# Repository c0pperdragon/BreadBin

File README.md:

# BreadBin computer
A CPU made of 7400 logic on breadboards - inside a bread bin ;-) 

## Current design 

After various experiments and failed attempts to design a 7400-based computer, I came to a quite minimalistic
8-bit approach which is nevertheless pretty versatile and can utilize a surprisingly large amount of memory
resources. The CPU core itself executes its program from a static 64K flash memory and can access 32 bytes of
internal RAM (which can be considered registers for all practical purposes). Access to the external memory 
area (up to 16MB of address space) allows addition of RAM, ROM and memory mapped IO. In the current setup this
directly mirrors the capabilities of my [OS816 reference design](https://github.com/c0pperdragon/OS816).

## Computer case

With the CPU already built so nicely on an actual wooden board, I had the idea to put it together with
the rest of the computer into a matching bread bin. Because the machine will not require any ventilation this
will keep the dust out quite reliably.

## On bread boards

Since a very long time I wanted to design my own CPU and build it from smaller parts, preferable 
on bread boards. My main problem with the approach were my bad experiences with bread boards as a whole,
as they seemed to be too unreliable for anything more serious than arduino tinkering.
As it turns out it is only a matter of using high-quality boards and cabling to get a reliably working
build. The boards I now use (BB830 from BusBoard) are quite expensive, but worth every penny 
and give me very little trouble.

In previous attempts I had much trouble to get a stable ground reference accross all the individual boards.
So this time I directly soldered together ground rails of parallel boards with silver wire on the bottom
and then placed the boards on top of a large plane of aluminium foil. This foil should make good contact to all
the silver ground wires to connect them together and additionally work as shielding. 
So far this works pretty good.

When using this kind of setup it is important to also use a matching logic family of chips. 74AC, 74ACT, 74LVC or 
others have a very fast switching characteristics. This is great for many applications but in a large build with
long and unshielded cables, their brutally steep signal edges wreck havoc with signal integritiy.
So I settled for the moderately fast and well-behaved 74HC logic ICs with only a few 74AC parts to speed up the ALU.

## Software

One of the hardest parts of home-made computers is to actually build all the software to make the machine useful.
To get the benefit of existing software, the breadboard computer core is designed to emulate the existing CPU
65C816. Together with 512K RAM and 512K Flash and identical IO capabilities, this now is a completely software 
compatible replica of the OS816 system - running at a lower overall speed, of course.

To properly stay in the "bread" theme, the emulator is called [Bernd](bernd) or BER/ND (if you like a 
more technical appearance). People familiar with the german TV station "Kinderkanal" will recognize the reference.

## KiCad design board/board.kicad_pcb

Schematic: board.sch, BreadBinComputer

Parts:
C1, C2: 33pF; C_Disc_D4.7mm_W2.5mm_P5.00mm
C3: 10uF; C_Disc_D4.7mm_W2.5mm_P5.00mm
C4: 100uF; CP_Radial_D10.0mm_P5.00mm
IN1: 74HC245; DIP-20_W7.62mm
INV1: 74HC04; DIP-14_W7.62mm
JIN1: Conn_01x08; PinHeader_1x08_P2.54mm_Vertical
JOUT1: Conn_01x08; PinHeader_1x08_P2.54mm_Vertical
JPOWER1: Conn_01x02; PinHeader_1x02_P2.54mm_Vertical
OR2: 74HC32; DIP-14_W7.62mm
OUT1: 74HC574; DIP-20_W7.62mm
R1: 1k; R_Axial_DIN0204_L3.6mm_D1.6mm_P7.62mm_Horizontal
R2: 1M; R_Axial_DIN0204_L3.6mm_D1.6mm_P7.62mm_Horizontal
R3: 33k; R_Axial_DIN0204_L3.6mm_D1.6mm_P7.62mm_Horizontal
RAM1: AS6C4008; DIP-32_W15.24mm
RES1: 74HC164; DIP-14_W7.62mm
RN1: 10k; R_Array_SIP9
ROM1: SST39SF040; DIP-32_W15.24mm
TIM1: NE555; DIP-8_W7.62mm
Y1: Crystal; Crystal_HC18-U_Vertical

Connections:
/AD0: RAM1.1, ROM1.12; also elsewhere on the board
/AD1: RAM1.2, ROM1.11; also elsewhere on the board
/AD2: RAM1.3, ROM1.10; also elsewhere on the board
/AD3: RAM1.4, ROM1.9; also elsewhere on the board
/AD4: RAM1.5, ROM1.8; also elsewhere on the board
/AD5: RAM1.6, ROM1.7; also elsewhere on the board
/AD6: RAM1.7, ROM1.6; also elsewhere on the board
/AD7: RAM1.8, ROM1.5; also elsewhere on the board
/AD8: RAM1.27, ROM1.27; also elsewhere on the board
/AD9: RAM1.28, ROM1.26; also elsewhere on the board
/AD10: RAM1.31, ROM1.23; also elsewhere on the board
/AD11: RAM1.30, ROM1.25; also elsewhere on the board
/AD12: RAM1.9, ROM1.4; also elsewhere on the board
/AD13: RAM1.26, ROM1.28; also elsewhere on the board
/AD14: RAM1.25, ROM1.29; also elsewhere on the board
/AD15: RAM1.10, ROM1.3; also elsewhere on the board
/AD16: RAM1.11, ROM1.2; also elsewhere on the board
/AD17: RAM1.23, ROM1.30; also elsewhere on the board
/AD18: RAM1.12, ROM1.1; also elsewhere on the board
/AD22: INV1.13, OR2.1; also elsewhere on the board
/AD23: INV1.11, OR2.2, OR2.4; also elsewhere on the board
/BreadBinCPU/CLK: INV1.6, RES1.8; also elsewhere on the board
/BreadBinCPU/RES#: RES1.13; also elsewhere on the board
/D0: IN1.9 (A7), OUT1.9, RAM1.13, ROM1.13; also elsewhere on the board
/D1: IN1.8 (A6), OUT1.8, RAM1.14, ROM1.14; also elsewhere on the board
/D2: IN1.7 (A5), OUT1.7, RAM1.15, ROM1.15; also elsewhere on the board
/D3: IN1.6 (A4), OUT1.6, RAM1.17, ROM1.17; also elsewhere on the board
/D4: IN1.5 (A3), OUT1.5, RAM1.18, ROM1.18; also elsewhere on the board
/D5: IN1.4 (A2), OUT1.4, RAM1.19, ROM1.19; also elsewhere on the board
/D6: IN1.3 (A1), OUT1.3, RAM1.20, ROM1.20; also elsewhere on the board
/D7: IN1.2 (A0), OUT1.2, RAM1.21, ROM1.21; also elsewhere on the board
/IOSEL#: OR2.6, OR2.9, OR2.12
/RAMSEL#: OR2.3, RAM1.22
/RD#: OR2.13, RAM1.24, ROM1.24; also elsewhere on the board
/ROMSEL#: INV1.10, ROM1.22
/WR#: OR2.10, RAM1.29, ROM1.31; also elsewhere on the board
unnamed: C1.1, R1.2, Y1.2
unnamed: C2.1, INV1.1, R2.2, Y1.1
unnamed: C3.1, R3.1, TIM1.2 (TR), TIM1.6 (THR)
unnamed: IN1.11 (B7), JIN1.1, RN1.9
unnamed: IN1.12 (B6), JIN1.2, RN1.8
unnamed: IN1.13 (B5), JIN1.3, RN1.7
unnamed: IN1.14 (B4), JIN1.4, RN1.6
unnamed: IN1.15 (B3), JIN1.5, RN1.5
unnamed: IN1.16 (B2), JIN1.6, RN1.4
unnamed: IN1.17 (B1), JIN1.7, RN1.3
unnamed: IN1.18 (B0), JIN1.8, RN1.2
unnamed: IN1.19 (CE), OR2.11
unnamed: INV1.2, INV1.3, R1.1, R2.1
unnamed: INV1.4, INV1.5, INV1.9
unnamed: INV1.12, OR2.5
unnamed: JOUT1.1, OUT1.12
unnamed: JOUT1.2, OUT1.13
unnamed: JOUT1.3, OUT1.14
unnamed: JOUT1.4, OUT1.15
unnamed: JOUT1.5, OUT1.16
unnamed: JOUT1.6, OUT1.17
unnamed: JOUT1.7, OUT1.18
unnamed: JOUT1.8, OUT1.19
unnamed: OR2.8, OUT1.11
unnamed: RES1.9, TIM1.3 (Q)

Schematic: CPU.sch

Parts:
DEC1: 74HC138; DIP-16_W7.62mm
GATE1: 74HC541; DIP-20_W7.62mm
IR1: 74HC574; DIP-20_W7.62mm
MCODE1: SST39SF040; DIP-32_W15.24mm
OP1: 74HC377; DIP-20_W7.62mm
OR1: 74HC32; DIP-14_W7.62mm
PC1, PC2: 74HC163; DIP-16_W7.62mm
PC3: 74HC377; DIP-20_W7.62mm
REG1: IDT71256; DIP-28_W7.62mm
UA1: 74HC377; DIP-20_W7.62mm
UB1: 74HC377; DIP-20_W7.62mm
UC1: 74HC377; DIP-20_W7.62mm

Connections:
/AD0: OR1.10, UA1.2, UB1.3; also elsewhere on the board
/AD1: UA1.5, UB1.4; also elsewhere on the board
/AD2: UA1.6, UB1.7; also elsewhere on the board
/AD3: UA1.9, UB1.8; also elsewhere on the board
/AD4: UA1.12, UB1.13; also elsewhere on the board
/AD5: UA1.15, UB1.14; also elsewhere on the board
/AD6: UA1.16, UB1.17; also elsewhere on the board
/AD7: UA1.19, UB1.18; also elsewhere on the board
/AD8: UB1.2, UC1.3; also elsewhere on the board
/AD9: UB1.5, UC1.4; also elsewhere on the board
/AD10: UB1.6, UC1.7; also elsewhere on the board
/AD11: UB1.9, UC1.8; also elsewhere on the board
/AD12: UB1.12, UC1.13; also elsewhere on the board
/AD13: UB1.15, UC1.14; also elsewhere on the board
/AD14: UB1.16, UC1.17; also elsewhere on the board
/AD15: UB1.19, UC1.18; also elsewhere on the board
/AD16: UC1.2; also elsewhere on the board
/AD17: UC1.5; also elsewhere on the board
/AD18: UC1.6; also elsewhere on the board
/AD22: UC1.16; also elsewhere on the board
/AD23: UC1.19; also elsewhere on the board
/BreadBinCPU/ALU/OP0: OP1.9; also elsewhere on the board
/BreadBinCPU/ALU/OP1: OP1.6; also elsewhere on the board
/BreadBinCPU/ALU/OP2: OP1.5; also elsewhere on the board
/BreadBinCPU/ALU/OP3: OP1.2; also elsewhere on the board
/BreadBinCPU/ALU/Q0: GATE1.2 (A0); also elsewhere on the board
/BreadBinCPU/ALU/Q1: GATE1.3 (A1); also elsewhere on the board
/BreadBinCPU/ALU/Q2: GATE1.4 (A2); also elsewhere on the board
/BreadBinCPU/ALU/Q3: GATE1.5 (A3); also elsewhere on the board
/BreadBinCPU/ALU/Q4: GATE1.6 (A4); also elsewhere on the board
/BreadBinCPU/ALU/Q5: GATE1.7 (A5); also elsewhere on the board
/BreadBinCPU/ALU/Q6: GATE1.8 (A6); also elsewhere on the board
/BreadBinCPU/ALU/Q7: GATE1.9 (A7); also elsewhere on the board
/BreadBinCPU/BRA#: OR1.8, PC1.9 (~PE), PC2.9 (~PE)
/BreadBinCPU/C3: UC1.9
/BreadBinCPU/C4: UC1.12
/BreadBinCPU/C5: UC1.15
/BreadBinCPU/CLK: GATE1.1 (G1), IR1.11, OP1.11, OR1.1, OR1.12, PC1.2 (CP), PC2.2 (CP), PC3.11, REG1.20, UA1.11, UB1.11, UC1.11; also elsewhere on the board
/BreadBinCPU/CMD0: DEC1.1, IR1.17
/BreadBinCPU/CMD1: DEC1.2, IR1.18, OR1.5
/BreadBinCPU/CMD2: DEC1.3, IR1.19, OR1.4
/BreadBinCPU/CMDBRE#: DEC1.9, OR1.9
/BreadBinCPU/CMDIN#: DEC1.14, OR1.13
/BreadBinCPU/CMDJMP#: DEC1.7, PC1.1 (~MR), PC2.1 (~MR), PC3.1
/BreadBinCPU/CMDOP#: DEC1.12, OP1.1
/BreadBinCPU/CMDOUT#: DEC1.13, OR1.2
/BreadBinCPU/CMDSET#: DEC1.15, GATE1.19 (G2)
/BreadBinCPU/CMDX#: DEC1.11, UA1.1, UB1.1, UC1.1
/BreadBinCPU/PAR0: IR1.12, OP1.8, PC1.6 (D3), REG1.5
/BreadBinCPU/PAR1: IR1.13, OP1.7, PC2.3 (D0), REG1.4
/BreadBinCPU/PAR2: IR1.14, OP1.4, PC2.4 (D1), REG1.3
/BreadBinCPU/PAR3: IR1.15, OP1.3, PC2.5 (D2), REG1.2
/BreadBinCPU/PAR4: IR1.16, PC2.6 (D3), REG1.1
/BreadBinCPU/RES#: MCODE1.2; also elsewhere on the board
/D0: GATE1.18 (Y0), PC3.3, REG1.19, UA1.3; also elsewhere on the board
/D1: GATE1.17 (Y1), PC3.4, REG1.18, UA1.4; also elsewhere on the board
/D2: GATE1.16 (Y2), PC3.7, REG1.17, UA1.7; also elsewhere on the board
/D3: GATE1.15 (Y3), PC3.8, REG1.16, UA1.8; also elsewhere on the board
/D4: GATE1.14 (Y4), PC3.13, REG1.15, UA1.13; also elsewhere on the board
/D5: GATE1.13 (Y5), PC3.14, REG1.13, UA1.14; also elsewhere on the board
/D6: GATE1.12 (Y6), PC3.17, REG1.12, UA1.17; also elsewhere on the board
/D7: GATE1.11 (Y7), PC3.18, REG1.11, UA1.18; also elsewhere on the board
/RD#: OR1.11; also elsewhere on the board
/WR#: OR1.3; also elsewhere on the board
unnamed: IR1.2, MCODE1.21
unnamed: IR1.3, MCODE1.20
unnamed: IR1.4, MCODE1.19
unnamed: IR1.5, MCODE1.18
unnamed: IR1.6, MCODE1.17
unnamed: IR1.7, MCODE1.15
unnamed: IR1.8, MCODE1.14
unnamed: IR1.9, MCODE1.13
unnamed: MCODE1.3, PC3.19
unnamed: MCODE1.4, PC3.12
unnamed: MCODE1.5, PC2.11 (Q3)
unnamed: MCODE1.6, PC2.12 (Q2)
unnamed: MCODE1.7, PC2.13 (Q1)
unnamed: MCODE1.8, PC2.14 (Q0)
unnamed: MCODE1.9, PC1.11 (Q3)
unnamed: MCODE1.10, PC1.12 (Q2)
unnamed: MCODE1.11, PC1.13 (Q1)
unnamed: MCODE1.12, PC1.14 (Q0)
unnamed: MCODE1.23, PC3.6
unnamed: MCODE1.25, PC3.9
unnamed: MCODE1.26, PC3.5
unnamed: MCODE1.27, PC3.2
unnamed: MCODE1.28, PC3.15
unnamed: MCODE1.29, PC3.16
unnamed: OR1.6, REG1.27
unnamed: PC1.15 (TC), PC2.7 (CEP)

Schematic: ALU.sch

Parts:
ADD1, ADD2: 74AC283; DIP-16_W7.62mm
AND1, AND2: 74AC08; DIP-14_W7.62mm
AND3, AND4: 74AC11; DIP-14_W7.62mm
LOGIC1, LOGIC2: 74AC00; DIP-14_W7.62mm
MUX1, MUX2, MUX3, MUX4: 74AC153; DIP-16_W7.62mm

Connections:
/AD0: AND1.1, AND3.10; also elsewhere on the board
/AD1: AND1.4, AND3.9; also elsewhere on the board
/AD2: AND1.9, AND3.5; also elsewhere on the board
/AD3: AND1.12, AND3.4; also elsewhere on the board
/AD4: AND2.1, AND3.3; also elsewhere on the board
/AD5: AND2.4, AND3.13; also elsewhere on the board
/AD6: AND2.9, AND3.2; also elsewhere on the board
/AD7: AND2.12, AND3.1; also elsewhere on the board
/AD8: ADD1.6, LOGIC1.10; also elsewhere on the board
/AD9: ADD1.2, LOGIC1.13; also elsewhere on the board
/AD10: ADD1.15, LOGIC1.4; also elsewhere on the board
/AD11: ADD1.11, LOGIC1.1; also elsewhere on the board
/AD12: ADD2.6, LOGIC2.10; also elsewhere on the board
/AD13: ADD2.2, LOGIC2.13; also elsewhere on the board
/AD14: ADD2.15, LOGIC2.4; also elsewhere on the board
/AD15: ADD2.11, LOGIC2.1; also elsewhere on the board
/BreadBinCPU/ALU/ADD0: ADD1.4, MUX1.6
/BreadBinCPU/ALU/ADD1: ADD1.1, MUX1.10
/BreadBinCPU/ALU/ADD2: ADD1.13, MUX2.6
/BreadBinCPU/ALU/ADD3: ADD1.10, MUX2.10
/BreadBinCPU/ALU/ADD4: ADD2.4, MUX3.6
/BreadBinCPU/ALU/ADD5: ADD2.1, MUX3.10
/BreadBinCPU/ALU/ADD6: ADD2.13, MUX4.6
/BreadBinCPU/ALU/ADD7: ADD2.10, MUX4.10
/BreadBinCPU/ALU/NND0: LOGIC1.8, MUX1.4
/BreadBinCPU/ALU/NND1: LOGIC1.11, MUX1.12
/BreadBinCPU/ALU/NND2: LOGIC1.6, MUX2.4
/BreadBinCPU/ALU/NND3: LOGIC1.3, MUX2.12
/BreadBinCPU/ALU/NND4: LOGIC2.8, MUX3.4
/BreadBinCPU/ALU/NND5: LOGIC2.11, MUX3.12
/BreadBinCPU/ALU/NND6: LOGIC2.6, MUX4.4
/BreadBinCPU/ALU/NND7: LOGIC2.3, MUX4.12
/BreadBinCPU/ALU/OP0: MUX1.14, MUX2.14, MUX3.14, MUX4.14; also elsewhere on the board
/BreadBinCPU/ALU/OP1: MUX1.2, MUX2.2, MUX3.2, MUX4.2; also elsewhere on the board
/BreadBinCPU/ALU/OP2: AND3.11; also elsewhere on the board
/BreadBinCPU/ALU/OP3: AND1.2, AND1.5, AND1.10, AND1.13, AND2.2, AND2.5, AND2.10, AND2.13; also elsewhere on the board
/BreadBinCPU/ALU/OVF: ADD2.9, MUX1.5
/BreadBinCPU/ALU/Q0: MUX1.7; also elsewhere on the board
/BreadBinCPU/ALU/Q1: MUX1.9; also elsewhere on the board
/BreadBinCPU/ALU/Q2: MUX2.7; also elsewhere on the board
/BreadBinCPU/ALU/Q3: MUX2.9; also elsewhere on the board
/BreadBinCPU/ALU/Q4: MUX3.7; also elsewhere on the board
/BreadBinCPU/ALU/Q5: MUX3.9; also elsewhere on the board
/BreadBinCPU/ALU/Q6: MUX4.7; also elsewhere on the board
/BreadBinCPU/ALU/Q7: MUX4.9; also elsewhere on the board
/BreadBinCPU/ALU/X0: ADD1.5, AND1.3, LOGIC1.9, MUX4.13
/BreadBinCPU/ALU/X1: ADD1.3, AND1.6, LOGIC1.12, MUX4.3
/BreadBinCPU/ALU/X2: ADD1.14, AND1.8, LOGIC1.5, MUX3.13
/BreadBinCPU/ALU/X3: ADD1.12, AND1.11, LOGIC1.2, MUX3.3
/BreadBinCPU/ALU/X4: ADD2.5, AND2.3, LOGIC2.9, MUX2.13
/BreadBinCPU/ALU/X5: ADD2.3, AND2.6, LOGIC2.12, MUX2.3
/BreadBinCPU/ALU/X6: ADD2.14, AND2.8, LOGIC2.5, MUX1.13
/BreadBinCPU/ALU/X7: ADD2.12, AND2.11, LOGIC2.2, MUX1.3
unnamed: ADD1.7, AND4.12
unnamed: ADD1.9, ADD2.7
unnamed: AND3.6, AND4.2
unnamed: AND3.8, AND4.13
unnamed: AND3.12, AND4.1

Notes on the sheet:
ALU operation summary 0000 B 0001 ZERO 0010 FF 0011 ZERO 0100 CRY B+1 if A=255, else B 0101 TOP 1, if A=255 and B=255 0110 FF 0111 ZERO 1000 ADD (A+B) mod 255 1001 OVF 1, if A+B>255 1010 NAND A NAND B 1011 REV revert bit order of A 1100 CRY1 A+B+1 if A=255, else A+B 1101 OVF1 1, if A+B+1>255 1110 N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

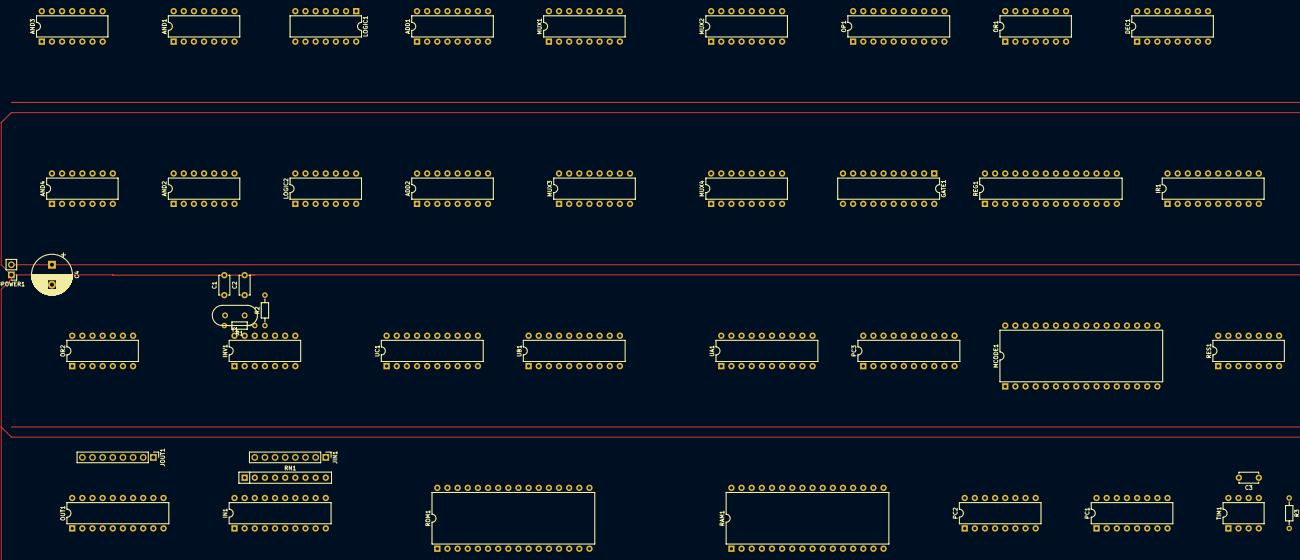
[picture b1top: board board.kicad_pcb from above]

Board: 2 copper layers, 45 parts (0 on the bottom side), 147 nets.

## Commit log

2020-10-26 Migrate from project ByteMachine
2020-10-29 Working on system board
2020-10-31 Finished design of system board
2020-11-01 Ongoing tweaks
2020-11-10 Adjusting hardware to better fit 7400 parts. Small test program.
2020-11-11 Extend IO address range to 512 bytes. Allows to map a complete page (256 bytes) of main address range to the extended RAM.
2020-11-11 Extend clock for all IO accesses - not only read access.
2020-11-12 Introduce a few bit of 74AC logic parts to speed up some critical signals. Use two 74HC gates in tandem to create a more stable clock.
2020-11-14 Documentation and Pictures
2020-11-14 Export schematics to PDF
2020-11-14 Formatting doc
2020-11-14 Formatting
2020-11-18 Simple emulator and a few more sample programs
2020-11-19 Try a to use a programming approach without having a stack at all. This leads to smaller and faster programes, but no recursion is possible.
2020-11-22 Change CPU control to only use HC parts while not losing speed. It is still possible to run at 11MHz.
2020-11-26 Add immediate addressing mode to DP instruction.
2020-11-27 Start working on "BER/ND", the control software for the BreadBin
2020-11-28 Serial IO programming
2020-11-30 Working serial IO with RTS/CTS on my FT232 USB-to-UART bridge
2020-12-08 First implementation of 16-bit multiplication library.
2020-12-08 Simplify 16-bit multiplication
2020-12-09 Implement division 16bit/8bit
2020-12-10 Implement prime number calculator as test program
2020-12-12 Example program to do some serious number crunching. The machine is not running stable yet.
2021-04-07 New attempt to create a part-reduced microcontroller architecture
2021-04-10 Modify wiring to for convenient breadboarding
2021-04-12 Complete redesign of basically everything
2021-04-12 Rework tooling for new architecture
2021-04-13 Get first test program to run
2021-04-15 Design system breadboard Adjust emulator for new architecture
2021-04-15 Prepare sample program to use the full BreadBin computer
2021-04-17 Start working on BER/ND
2021-04-17 Add macro feature to assembler.
2021-04-18 Emulated Bernd runs its first test program (very limited instruction set)
2021-04-19 Redesign memory/io interface for easier wireing on the breadboard. This also uses less ICs.
2021-04-19 Fixed address decoding
2021-04-24 Restructure memory map for easier compatibility with other designs
2021-04-27 Fine-tune resistors of the oscillator
2021-04-30 Implement enough instructions to actually execute the first OS816 example.
2021-04-30 Change branch instruction to only use the B operator.
2021-04-30 No longer commit .hex and .lst files
2021-04-30 Change address latch interface and software access. Refactor large parts of Bernd to work with new latch interface and make code more compact also.
2021-04-30 Typos
2021-05-01 Restructure ALU operations to better match Bernd's needs. And it is also easier to implement the ALU with logic ICs.
2021-05-01 Streamline some instructions
2021-05-02 Bugfixes, more instructions.
2021-05-13 More instructions. Fix the ASL crash.
2021-05-15 More instructions, add serial input to emulator
2021-05-15 More instructions as needed by OS816
2021-05-16 Implement BRL instruction
2021-05-19 Simplify ALU to only 6 operations. Simplify branch operation to check only one bit
2021-05-22 Rework ALU and opoerand stack so it can be easier implemented in 7400 logic
2021-05-23 Refactoring bernd
2021-05-23 Include proper NOP instruction
2021-05-23 Rework schematic for modified architecture
2021-05-24 Complete ALU design
2021-05-24 Adjust toolchain to new ALU definition and adjust Bernd to make use of it
2021-05-30 Modify schematic to better match breadboard possibilities.
2021-05-31 Modify ALU so I can build it with parts that are actually available.
2021-06-04 Rework ALU to have 4 operand inputs and so it can be built with availbale parts
2021-06-04 Modify ALU: Remove REV operation and get AVG/HALF/ROR instead.
2021-06-18 Work on ALU. Implement more 65c816 instructions.
2021-06-20 Adjust schematics to match actual breadboard
2021-06-27 Indexed addressing may cross bank boundaries
2021-07-01 Add a waitstate for reading main RAM
2021-07-02 Use a 1:2 clock duty cycle (33% low) no wait states are necessary
2021-07-02 Docu and pictures
2021-07-03 Add more instructions (and fix CMP)
2021-07-09 Emulator mode for board with only bare port IO (no serial communication)
2021-07-10 More instructions and more addressing modes
2021-07-11 Complete the opcode matrix
2021-07-11 Relax some restrictions. CPU halt on all the remaining ones.
2021-07-13 More instructions and V flag support.
2021-07-16 Check for uninitialized memory
2021-07-16 Fix incorrct XBA instruction.
2021-07-18 Turn off uninitialized check
2021-07-23 Support extended intex HEX format
2021-07-24 Fix addressing mode (d),y
2021-07-27 Speed up MVN instruction a bit
2021-07-30 Provide input as individual keys.
2021-08-22 Simulate ROM write sequence
2021-08-27 Start with data length flags to 16 bit
2021-08-28 Change serial port input lines to bit 7&6 on input port
2021-08-29 Fix BIT instruction. Read characters without blocking.
2021-08-30 Add some timing calculations
2021-09-12 Support FLASH sector erase
2021-09-13 Add waitstate for read operations, do some optimizations
2021-09-19 Start execution from $FFFFF8 to match new memory map of OS816
2021-09-19 Upload pics
2021-09-23 Documentation
2021-09-29 Docu
2021-11-12 Adjust memory map for emulation to fit OS816 Rev.3
2021-11-21 Rework MMU to use a 74HC138 as in the OS816 reference
